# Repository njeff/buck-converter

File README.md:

# Buck Converter Refresher

All the simulation, visualization, and PCB data used in the making of my buck converter refresher project.

WIP

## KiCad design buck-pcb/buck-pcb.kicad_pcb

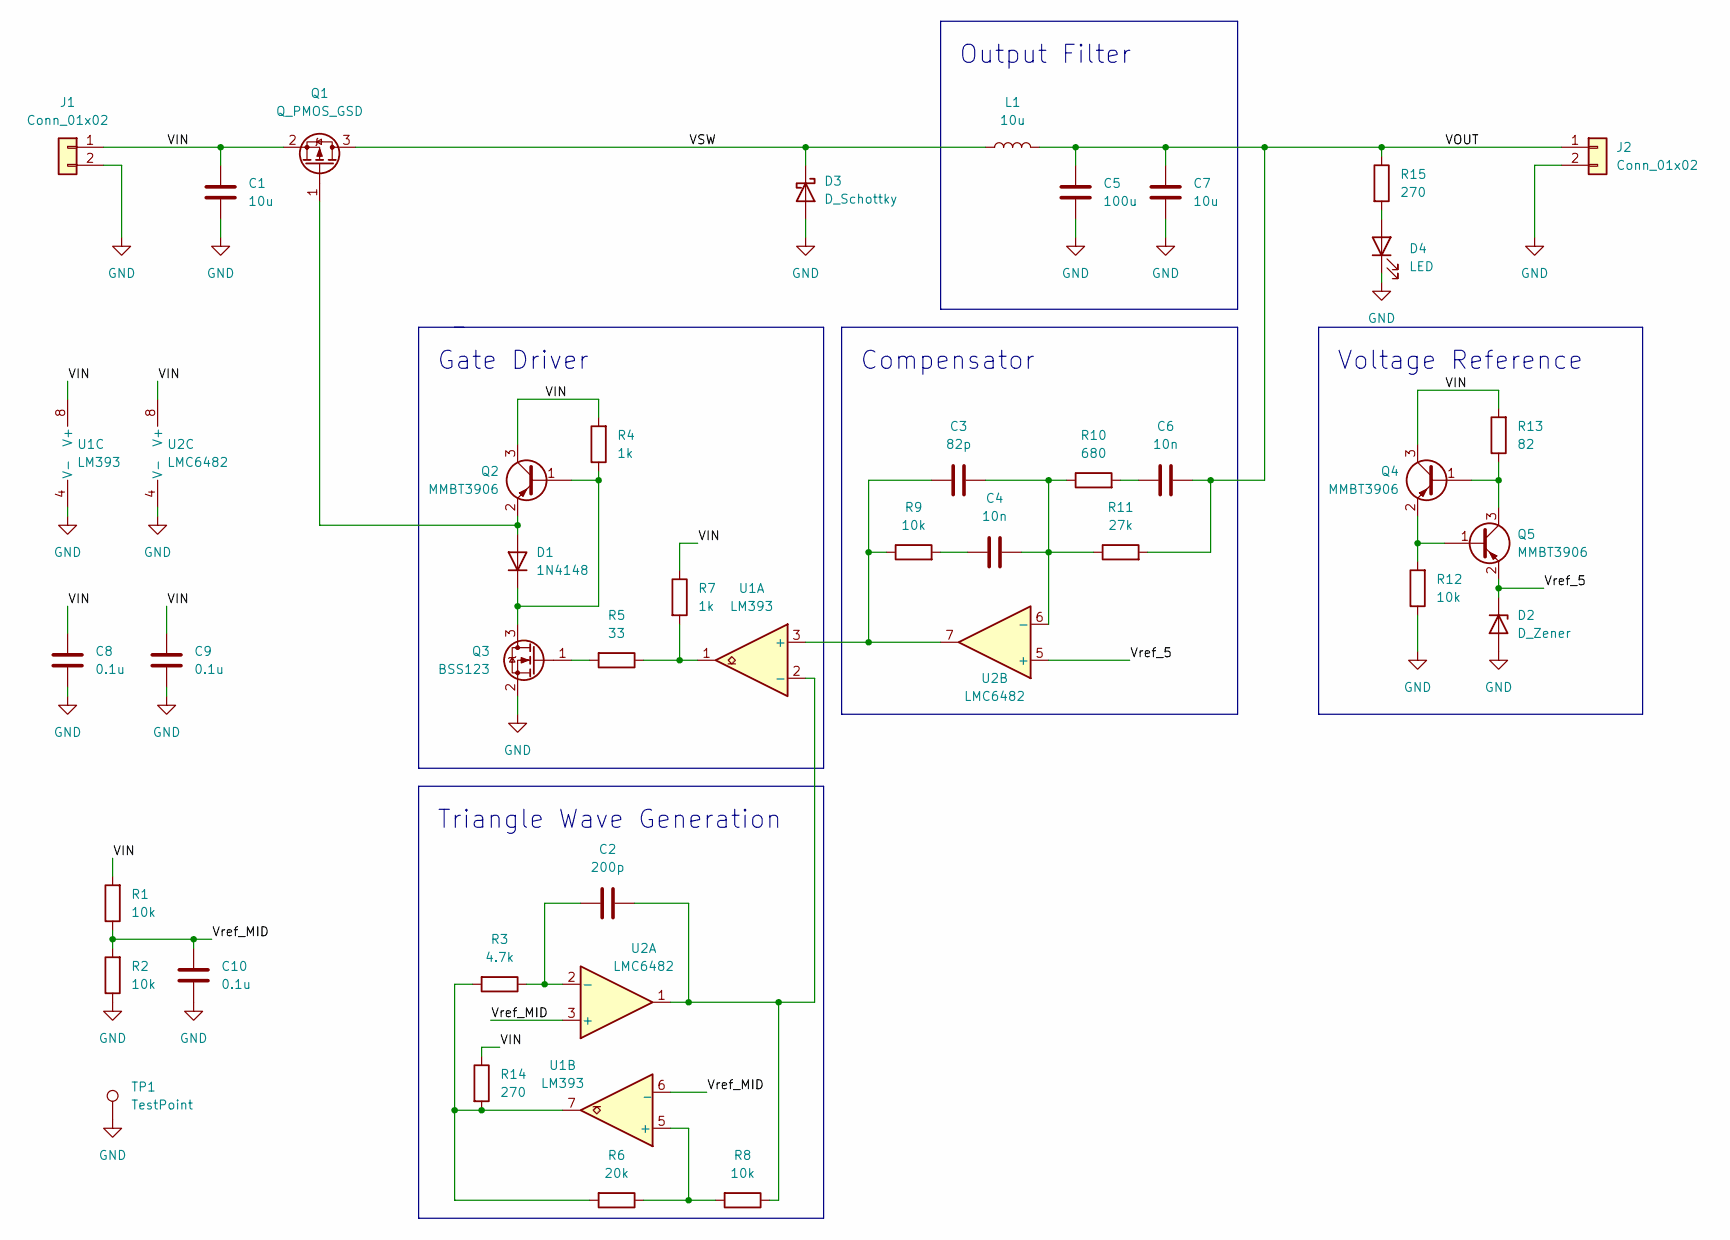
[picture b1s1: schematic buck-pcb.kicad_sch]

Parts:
C1, C7: 10u; C_0603_1608Metric
C2: 200p; C_0603_1608Metric
C3: 82p; C_0603_1608Metric
C4, C6: 10n; C_0603_1608Metric
C5: 100u; CP_Elec_6.3x4.9
C8, C9, C10: 0.1u; C_0603_1608Metric
D1: 1N4148; D_SOD-323_HandSoldering
D2: D_Zener; D_SOD-123
D3: D_Schottky; D_SMB
D4: LED; LED_0603_1608Metric
J1, J2: Conn_01x02; PinHeader_1x02_P2.54mm_Vertical
L1: 10u; BMRx00060630
Q1: Q_PMOS_GSD; SOT-23
Q2, Q4, Q5: MMBT3906; SOT-23
Q3: BSS123; SOT-23
R1, R2, R8, R9, R12: 10k; R_0603_1608Metric
R3: 4.7k; R_0603_1608Metric
R4, R7: 1k; R_0603_1608Metric
R5: 33; R_0603_1608Metric
R6: 20k; R_0603_1608Metric
R10: 680; R_0603_1608Metric
R11: 27k; R_0603_1608Metric
R13: 82; R_0603_1608Metric
R14, R15: 270; R_0603_1608Metric
TP1: TestPoint; TestPoint_Keystone_5005-5009_Compact
U1: LM393; SOIC-8_3.9x4.9mm_P1.27mm
U2: LMC6482; SOIC-8_3.9x4.9mm_P1.27mm

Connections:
/VIN: C1.1, C8.1, C9.1, J1.1, Q1.2 (S), Q2.3 (C), Q4.3 (C), R1.2, R4.2, R7.1, R13.2, R14.1, U1.8 (V+), U2.8 (V+)
/VOUT: C5.1, C6.2, C7.1, J2.1, L1.2, R11.2, R15.1
/VSW: D3.1 (K), L1.1, Q1.3 (D)
/Vref_5: D2.1 (K), Q5.2 (E), U2.5 (+)
/Vref_MID: C10.1, R1.1, R2.2, U1.6 (_), U2.3 (+)
GND: C1.2, C5.2, C7.2, C8.2, C9.2, C10.2, D2.2 (A), D3.2 (A), D4.1 (K), J1.2, J2.2, Q3.2 (S), R2.1, R12.1, TP1.1, U1.4 (V-), U2.4 (V-)
unnamed: C2.1, R3.1, U2.2 (-)
unnamed: C2.2, R8.1, U1.2 (-), U2.1
unnamed: C3.1, R9.1, U1.3 (+), U2.7
unnamed: C3.2, C4.2, R10.1, R11.1, U2.6 (-)
unnamed: C4.1, R9.2
unnamed: C6.1, R10.2
unnamed: D1.1 (K), Q2.1 (B), Q3.3 (D), R4.1
unnamed: D1.2 (A), Q1.1 (G), Q2.2 (E)
unnamed: D4.2 (A), R15.2
unnamed: Q3.1 (G), R5.2
unnamed: Q4.1 (B), Q5.3 (C), R13.1
unnamed: Q4.2 (E), Q5.1 (B), R12.2
unnamed: R5.1, R7.2, U1.1
unnamed: R6.1, R8.2, U1.5 (+)
unnamed: R3.2, R6.2, R14.2, U1.7

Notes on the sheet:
Gate Driver
Output Filter
Compensator
Voltage Reference
Triangle Wave Generation

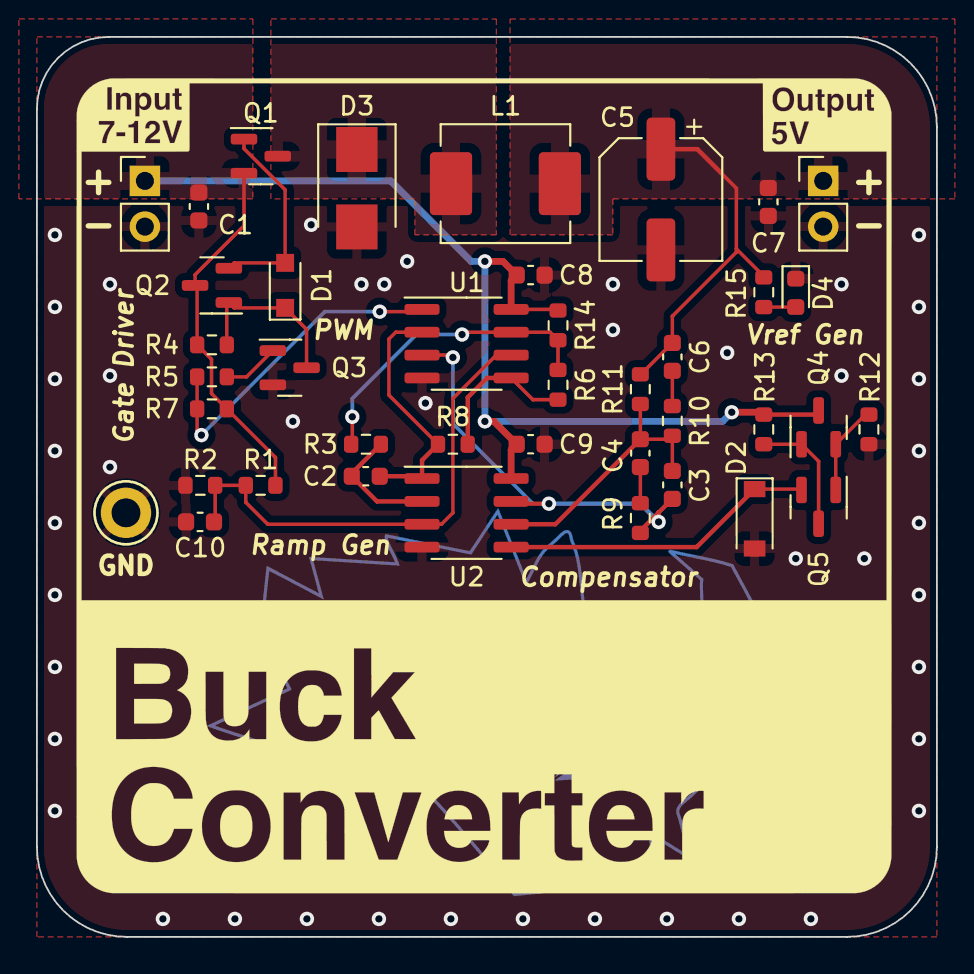
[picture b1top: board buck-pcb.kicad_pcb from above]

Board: 2 copper layers, 50.0 x 50.0 mm, 42 parts (1 on the bottom side), 21 nets.

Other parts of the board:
Ref**: Val**; pcb-inkscape
Ref**#2: Val**; pcb-art-back

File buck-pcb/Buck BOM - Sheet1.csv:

Source:,C:\Users\Jeffrey\Desktop\working\buck-converter\buck-pcb\buck-pcb.kicad_sch,,,,,,,,,,,,,,,,
Date:,2/20/2022 13:34,,,,,,,,,,,,,,,,
Tool:,Eeschema (6.0.2),,,,,,,,,,,,,,,,
Generator:,C:\Program Files\KiCad\6.0\bin\scripting\plugins/bom_csv_grouped_by_value_with_fp.py,,,,,,,,,,,,,,,,
Component Count:,36,,Multiple,3,,,,,,,,,,,,,
Ref,Qnty,Ext Qty,Value,Cmp name,Footprint,Description,Vendor,Notes,Mfgr Part Name,Digikey Name,Link,,,,,,
"C1, C7,",2,6,10u,C,Capacitor_SMD:C_0603_1608Metric,Unpolarized capacitor,,,TMK107BBJ106MA-T,587-6023-1-ND,https://www.digikey.com/en/products/detail/taiyo-yuden/TMK10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,,,,,,
"C2,",1,3,200p,C,Capacitor_SMD:C_0603_1608Metric,Unpolarized capacitor,,220p,CL10C221JB8NNNC,1276-1048-1-ND,https://www.digikey.com/en/products/detail/samsung-electro-m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,,,,,,
"C3,",1,3,82p,C,Capacitor_SMD:C_0603_1608Metric,Unpolarized capacitor,,,0603N820J500CT,1292-1547-1-ND,https://www.digikey.com/en/products/detail/walsin-technology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,,,,,,
"C4, C6,",2,6,10n,C,Capacitor_SMD:C_0603_1608Metric,Unpolarized capacitor,,,C0603C103K4HAC7867,399-C0603C103K4HAC7867CT-ND,https://www.digikey.com/en/products/detail/kemet/C0603C103K4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,,,,,,
"C5,",1,3,100u,C,Capacitor_SMD:CP_Elec_6.3x4.9,Unpolarized capacitor,,,865080343009,732-8419-1-ND,https://www.digikey.com/en/products/detail/w%C3%BCrth-elektr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,ESY107M050AG3AA,399-6119-ND,https://www.digikey.com/en/products/detail/kemet/ESY107M050A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,,,
"C8, C9,",2,6,0.1u,C,Capacitor_SMD:C_0603_1608Metric,Unpolarized capacitor,,,06033C104KAT4A,478-7018-1-ND,https://www.digikey.com/en/products/detail/kyocera-avx/06033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,,,,,,
"D1,",1,3,1N4148,D,Diode_SMD:D_SOD-323_HandSoldering,Diode,,,1N4148WS RRG,1N4148WSRRGCT-ND,https://www.digikey.com/en/products/detail/taiwan-semiconduc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,,,,,,
"D2,",1,3,D_Zener,D_Zener,Diode_THT:D_DO-41_SOD81_P7.62mm_Horizontal,Zener diode,,,SZMMSZ5231BT1G,SZMMSZ5231BT1GOSCT-ND,https://www.digikey.com/en/products/detail/onsemi/SZMMSZ5231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,,,,,,1N4733A-TR
"D3,",1,3,D_Schottky,D_Schottky,Diode_SMD:D_SMB,Schottky diode,,,B340B-13-F,B340B-FDICT-ND,https://www.digikey.com/en/products/detail/diodes-incorporat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,,,,,,
"D4,",1,3,LED,LED,LED_SMD:LED_0603_1608Metric,Light emitting diode,,,LA L296-Q2R2-1-0-20-R18-Z,475-2712-1-ND,https://www.digikey.com/en/products/detail/osram-opto-semico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,,,,,,
"J1, J2,",2,6,Conn_01x02,Conn_01x02,Connector_PinHeader_2.54mm:PinHeader_1x02_P2.54mm_Vertical,"Generic connector, single row, 01x02, script generated (kicad-library-utils/schlib/autogen/connector/)",,,,,,,,,,,
"L1,",1,3,10u,L,Inductor_SMD:L_7.3x7.3_H3.5,Inductor,,,BMRF00060630100MA1,2184-BMRF00060630100MA1CT-ND,https://www.digikey.com/en/products/detail/chilisin-electron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,,,,,,
"Q1,",1,3,Q_PMOS_GSD,Q_PMOS_GSD,Package_TO_SOT_SMD:SOT-23,"P-MOSFET transistor, gate/source/drain",,,DMP3125L-7,DMP3125L-7DICT-ND,https://www.digikey.com/en/products/detail/diodes-incorporat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,DMP3098LQ-7,DMP3098LQ-7DICT-ND,https://www.digikey.com/en/products/detail/diodes-incorporat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,,,
"Q2, Q4, Q5,",3,9,MMBT3906,MMBT3906,Package_TO_SOT_SMD:SOT-23,"-0.2A Ic, -40V Vce, Small Signal PNP Transistor, SOT-23",,,"MMBT3906,215",1727-4045-1-ND,https://www.digikey.com/en/products/detail/nexperia-usa-inc/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,,,,,,
"Q3,",1,3,BSS123,BSS123,Package_TO_SOT_SMD:SOT-23,"0.17A Id, 100V Vds, N-Channel MOSFET, SOT-23",,,BSS123K-TP,BSS123K-TPMSCT-ND,https://www.digikey.com/en/products/detail/micro-commercial-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,,,,,,
"R1, R2, R8, R9, R12,",5,15,10k,R,Resistor_SMD:R_0603_1608Metric,Resistor,,,RMCF0603JT10K0,RMCF0603JT10K0CT-ND,https://www.digikey.com/en/products/detail/stackpole-electro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,,,,,,
"R3,",1,3,4.7k,R,Resistor_SMD:R_0603_1608Metric,Resistor,,,RMCF0603JT4K70,RMCF0603JT4K70CT-ND,https://www.digikey.com/en/products/detail/stackpole-electro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,,,,,,
"R4, R7,",2,6,1k,R,Resistor_SMD:R_0603_1608Metric,Resistor,,,RMCF0603FG1K00,RMCF0603FG1K00CT-ND,https://www.digikey.com/en/products/detail/stackpole-electro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,,,,,,
"R5,",1,3,33,R,Resistor_SMD:R_0603_1608Metric,Resistor,,,RMCF0603JT33R0,RMCF0603JT33R0CT-ND,https://www.digikey.com/en/products/detail/stackpole-electro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,,,,,,
"R6,",1,3,20k,R,Resistor_SMD:R_0603_1608Metric,Resistor,,,RMCF0603JT20K0,RMCF0603JT20K0CT-ND,https://www.digikey.com/en/products/detail/stackpole-electro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,,,,,,
"R10,",1,3,680,R,Resistor_SMD:R_0603_1608Metric,Resistor,,,RMCF0603JT680R,RMCF0603JT680RCT-ND,https://www.digikey.com/en/products/detail/stackpole-electro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,,,,,,
"R11,",1,3,27k,R,Resistor_SMD:R_0603_1608Metric,Resistor,,,RMCF0603FT27K0,RMCF0603FT27K0CT-ND,https://www.digikey.com/en/products/detail/stackpole-electro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,,,,,,
"R13,",1,3,82,R,Resistor_SMD:R_0603_1608Metric,Resistor,,,RMCF0603JT82R0,RMCF0603JT82R0CT-ND,https://www.digikey.com/en/products/detail/stackpole-electro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,,,,,,
"R14, R15,",2,6,270,R,Resistor_SMD:R_0603_1608Metric,Resistor,,,RMCF0603JT270R,RMCF0603JT270RCT-ND,https://www.digikey.com/en/products/detail/stackpole-electro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,,,,,,
"U1,",1,3,LM393,LM393,Package_SO:SOIC-8_3.9x4.9mm_P1.27mm,"Low-Power, Low-Offset Voltage, Dual Comparators, DIP-8/SOIC-8/TO-99-8",,,LM393DR2G,LM393DR2GOSCT-ND,https://www.digikey.com/en/products/detail/onsemi/LM393DR2G/918527,,,,,,
"U2,",1,3,LMC6482,LMC6482,Package_SO:SOIC-8_3.9x4.9mm_P1.27mm,"Dual CMOS Rail-to-Rail Input and Output Operational Amplifier, DIP-8/SOIC-8, SSOP-8",,TL972,TL972ID,296-34315-5-ND,https://www.digikey.com/en/products/detail/texas-instruments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,,,,,,

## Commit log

2021-12-23 Plot generation init
2022-01-01 Diagrams, ESR initial
2022-01-01 ESR sim data
2022-01-01 ESR fig
2022-01-04 Averaging Model initial
2022-01-05 Steady-state pic
2022-01-05 Inital schematics for FB, more pics
2022-01-05 Stepped output
2022-01-05 Avg figures
2022-01-07 More SPICE sims
2022-01-28 Update fb-sch3, push-pull experiments
2022-02-10 Getting started with compensator sims
2022-02-14 Bode figures prelim
2022-02-17 Reorganizing files, updated ramp gen and compensator test
2022-02-17 Fiddling with compensator for figure, trying out different comparators
2022-02-18 Change ramp opamp, add PCB initial project
2022-02-18 Dropping in some components
2022-02-18 Adjusting CCM-DCM1 to be local, duplicating for now since I can't get local paths to work
2022-02-18 Added in PMOS and gate driver
2022-02-19 KiCAD schematic mostly done
2022-02-20 Putting together complete system
2022-02-20 FP assigned
2022-02-25 Initial layout
2022-02-28 Working on layout
2022-03-02 Added more PCB art
2022-03-02 Remove ai
2022-03-08 Gerbers sent
2022-03-08 Forgot to include the art files
2022-03-08 Actual BOM
2022-05-03 Working scope images
2022-06-09 Sim images
2022-06-09 Full sim plot
